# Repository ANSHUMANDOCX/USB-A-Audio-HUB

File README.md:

# USB A AUDIO HUB

## About
This is a USB A HUB along with a Audio Out/In port. This design uses PCM2912A along with SL2.1A 

- It has 3 downstream USB-A ports and 1 USB-C input so we can connect any desired length of cable we want to use with it
- TRRS audio jack for headphones with integrated microphone along with a mute/unmute switch built into the hub 
## Usage guide
- using it is as simple as it can be you just need to plug into the single usb C on the side and connected it to your device there are no driver needed 
- It doesnt need any firmware flashing 
- Its compatible with windows and linux 
## Assembly guide
All you need to do is place the PCB at the base plate align the holes and place the Body on top of it and screw the two parts using M3x8 countersunk screws.
## Parts used 
- TRRS Audio port
- USB A ports 
- PCM2912A
- SL2.1A
## Features
- USB 2.0 Full-Speed audio interface
- Stereo DAC output for headphones
- Microphone input with bias supply
- Integrated USB hub for multiple downstream devices
## PCB

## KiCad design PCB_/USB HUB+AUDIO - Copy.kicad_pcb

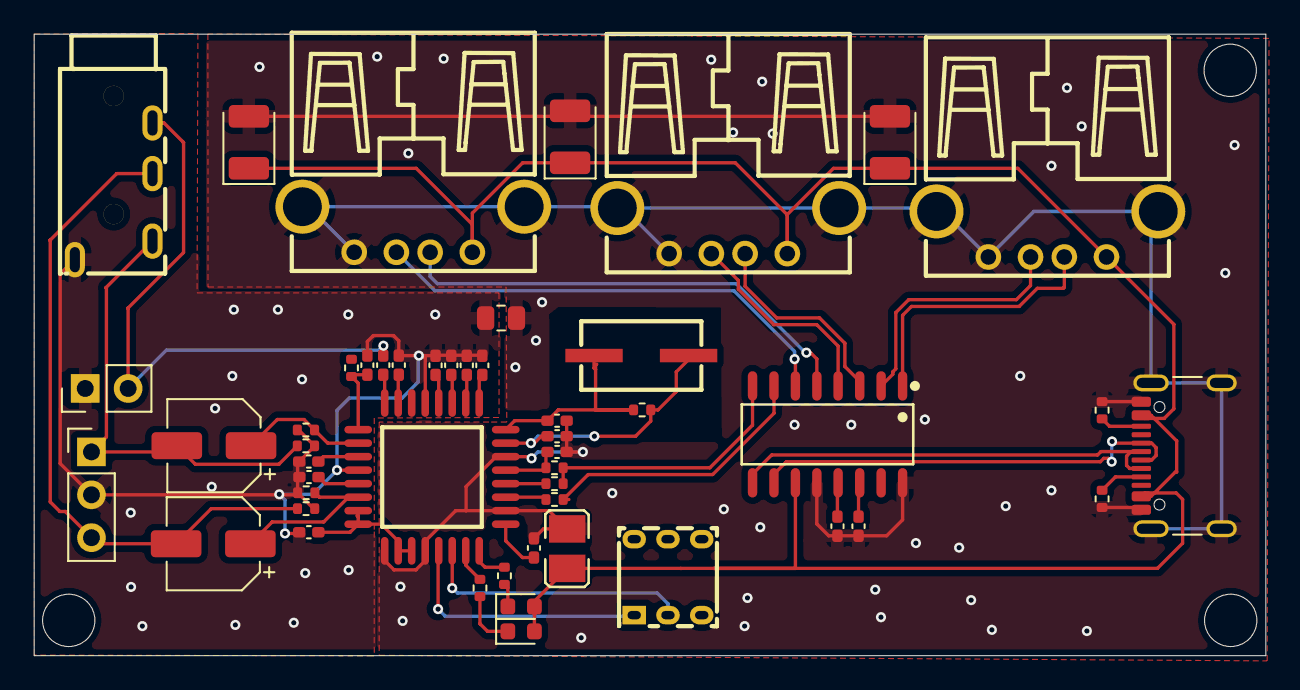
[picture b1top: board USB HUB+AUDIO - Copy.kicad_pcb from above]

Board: 2 copper layers, 73.0 x 36.8 mm, 46 parts (0 on the bottom side), 37 nets.

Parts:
C1: 1uf; C_0402_1005Metric_Pad0.74x0.62mm_HandSolder
C2, C3: 20pf; C_0402_1005Metric_Pad0.74x0.62mm_HandSolder
C4, C5: 100pf; C_0402_1005Metric_Pad0.74x0.62mm_HandSolder
C6, C10: 3.3uF; C_0402_1005Metric_Pad0.74x0.62mm_HandSolder
C7: 0.1uF; C_0402_1005Metric_Pad0.74x0.62mm_HandSolder
C8, C11, C17, C18: 1uF; C_0402_1005Metric_Pad0.74x0.62mm_HandSolder
C9: 0.22uF; C_0402_1005Metric_Pad0.74x0.62mm_HandSolder
C12, C14: 10uF; C_0402_1005Metric_Pad0.74x0.62mm_HandSolder
C13, C16: 100uF; CP_Elec_5x5.4
C15, C19, C20: C_Polarized; CP_EIA-3528-15_AVX-H
Cc14: 1uF; C_0402_1005Metric_Pad0.74x0.62mm_HandSolder
D1: REC; LED_0603_1608Metric
D2: PLAY; LED_0603_1608Metric
J7: USB_C_Receptacle_USB2.0_16P; USB_C_Receptacle_GCT_USB4105-xx-A_16P_TopMnt_Horizontal
J9: Conn_01x03_Pin; PinHeader_1x03_P2.54mm_Vertical
J10: Conn_01x02_Pin; PinHeader_1x02_P2.54mm_Vertical
L1: 1uH; L1008
R1, R2, R5, R7, R8, R10, R11: 22R; R_0402_1005Metric
R3: 1.5k; R_0402_1005Metric
R4: 1M; R_0402_1005Metric
R6: 5.1K; R_0402_1005Metric
R9: 5.1k; R_0402_1005Metric
R12, R13: 820R; R_0402_1005Metric
R20: 0; R_0805_2012Metric
SW2: XKB5858-Z-80; SW-TH_XKB5858-Z-80
U1: PCM2912APJTR; TQFP-32_L7.0-W7.0-P0.80-LS9.0-TL
U2: SL2.1A; SOP-16_L10.0-W3.9-P1.27-LS6.0-BL
U3: PJ-320A-4P DIP; AUDIO-TH_PJ-320A-4P-DIP
Y1: 6Mhz; CRYSTAL-SMD_L7.0-W4.0-LS7.8

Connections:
/DM1: R1.2, U2.7 (DM1)
/DP1: R2.2, R3.2, U2.8 (DP1)
D+: J7.A6 (D+), J7.B6 (D+), U2.10 (DP)
D-: J7.A7 (D-), J7.B7 (D-), U2.9 (DM)
GND: C1.1, C2.2, C3.2, C4.2, C5.2, C6.2, C7.2, C8.2, C10.1, C11.2, C12.2, C14.2, C15.2, C17.2, C18.1, C19.2, C20.2, Cc14.2, J7.A1 (GND), J7.A12 (GND), J7.B1 (GND), J7.B12 (GND), J7.S1 (SHIELD), J9.2, J10.1, L1.2, R6.2, R7.1, R8.2, R9.2, R10.2, R11.2, R20.1, R20.2, U1.2 (VBUS), U1.6 (DGND), U1.13 (AGND), U1.20 (HGND), U1.25 (PGND), U1.28 (TEST0), U2.12 (GND), U2.16 (XIN), U3.A
L: C13.2, J9.1, R8.1, U3.D
MIC: C9.1, J10.2, U3.B
unnamed: D1.1 (K), R12.2
unnamed: D2.1 (K), R13.2
unnamed: J7.A5 (CC1), R6.1
unnamed: J7.B5 (CC2), R9.1
unnamed: R13.1, U1.32 (#PLAY)
unnamed: R12.1, U1.31 (#REC)
unnamed: SW2.1, U1.29 (#SSPND)
unnamed: C18.2, U1.1 (BGND)
unnamed: R2.1, U1.4 (D+)
unnamed: R1.1, U1.3 (D-)
unnamed: C4.1, U1.9 (FL)
unnamed: C5.1, U1.10 (FR)
unnamed: C17.1, U1.23 (MAMP), U1.24 (POWER), U1.26 (VCCP), U1.27 (TEST1)
unnamed: C10.2, R5.1, U1.17 (MBIAS)
unnamed: SW2.2, U1.30 (MMUTE)
unnamed: C8.1, U1.15 (VCCA)
unnamed: C11.1, U1.19 (VCCL)
unnamed: Cc14.1, U1.21 (VCCR)
unnamed: C6.1, U1.11 (VCOM1)
unnamed: C7.1, U1.12 (VCOM2)
unnamed: C1.2, R3.1, U1.5 (VDD)
unnamed: C9.2, U1.16 (VIN)
unnamed: C13.1, R7.2, U1.18 (VOUTL)
unnamed: C16.1, R10.1, U1.22 (VOUTR)
unnamed: C3.1, R4.2, U1.8 (XTI), Y1.2
unnamed: C2.1, R4.1, U1.7 (XTO), Y1.1
unnamed: C12.1, U2.14 (VDD18)
unnamed: C14.1, U2.13 (VDD33)
R: C16.2, J9.3, R11.1, U3.C
VBUS: C15.1, C19.1, C20.1, D1.2 (A), D2.2 (A), J7.A4 (VBUS), J7.A9 (VBUS), J7.B4 (VBUS), J7.B9 (VBUS), L1.1, U2.11 (VDD5)
